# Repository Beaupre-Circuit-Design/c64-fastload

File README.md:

# Epyx FastLoad Cartridge

# Introduction

An open-source recreation of the Epyx FastLoad cartridge, this board can be used to repair a broken cartridge or build your own one. The main difference with other design are compatibility with 28 and 32 pin rom chips and bank configurability to allow multiple versions of the FastLoad rom to be installed on one cartridge.

# Compatibility

Since the design is almost identical to the original cartridge, it should have the same level of compatibility than the original FastLoad cartridge.

# Configuration

Unless dealing with special cases or custom software, J3 should be set to STD. A17 control the size of the of the EPROM, for 28 pin rom, short pin 1/2 or for 32 pin rom position 2-3 is used for bank switching.

## Bank Switching example

|A13|A14|A15|A16|A17|A18| Start of Bank |
|---|---|---|---|---|---|---------------|
|   |   |   |   |   |   |0x00000-0x01FFF|
| X |   |   |   |   |   |0x02000-0x03FFF|
|   | X |   |   |   |   |0x04000-0x05FFF|
| X | X |   |   |   |   |0x06000-0x07FFF|
|   |   | X |   |   |   |0x08000-0x09FFF|
| X |   | X |   |   |   |0x0A000-0x0BFFF|
|   | X | X |   |   |   |0x0C000-0x0DFFF|
| X | X | X |   |   |   |0x0E000-0x0FFFF|
...
|   |   |   | X |   |   |0x10000-0x11FFF|
...
|   |   |   |   | X |   |0x20000-0x21FFF|
...
|   |   |   | X | X |   |0x30000-0x31FFF|
...
|   |   |   |   |   | X |0x40000-0x41FFF|
...
|   |   |   | X |   | X |0x50000-0x51FFF|
...
|   |   |   |   | X | X |0x60000-0x61FFF|
...
|   |   |   | X | X | X |0x70000-0x71FFF|
...
| X | X | X | X | X | X |0x7E000-0x7FFFF|
| X |   | X | X | X | X |0x7A000-0x7FFFF|
|   | X | X | X | X | X |0x7C000-0x7CFFF|
| X | X | X | X | X | X |0x7E000-0x7FFFF|

# Components and assembly

[Gerbers files](Gerbers/) are available for uploading to your prefered manufacturer (I personnally use JLCPCB). In adition to the PCB, a few components must be sourced. If you want to save a few cents, R1-8 can all be 2K7 (Anything over 1K will probably work just fine too). As usual, start with the smallest components and build up (in this case, the sockets and capacitors are probably the smallest height you will have).

|Designator|Value                                |Total Quantity|
|----------|-------------------------------------|--------------|
|C1        |Ceramic Capacitor 470nF              |1             |
|C2-C3     |Ceramic Capacitor 100nF              |2             |
|R1-R7     |10K Resistor                         |7             |
|R8        |2K7 Resistor                         |1             |
|U1        |74LS07 DIP 14                        |1             |
|          |Optional DIP 14 Socket (7.62mm Wide) |1 (Optional)  |
|U2        |DIP 32 Socket (15.24mm Wide)         |1             |
|          |DIP28/32 EPROM                       |1             |
|SW1       |Push button momentary 6mm            |1             |

Once everything is assembled, program your eprom with the correct [rom image](Roms/), configure the board and you're done.

# Epyx FastLoad Manual

For reference, the Epyx FastLoad manual is available [here](Manual/).

# Licence

This work is licensed under the Creative Commons Attribution-NonCommercial-ShareAlike 4.0 International License. To view a copy of this license, visit http://creativecommons.org/licenses/by-nc-sa/4.0/ or send a letter to Creative Commons, PO Box 1866, Mountain View, CA 94042, USA.

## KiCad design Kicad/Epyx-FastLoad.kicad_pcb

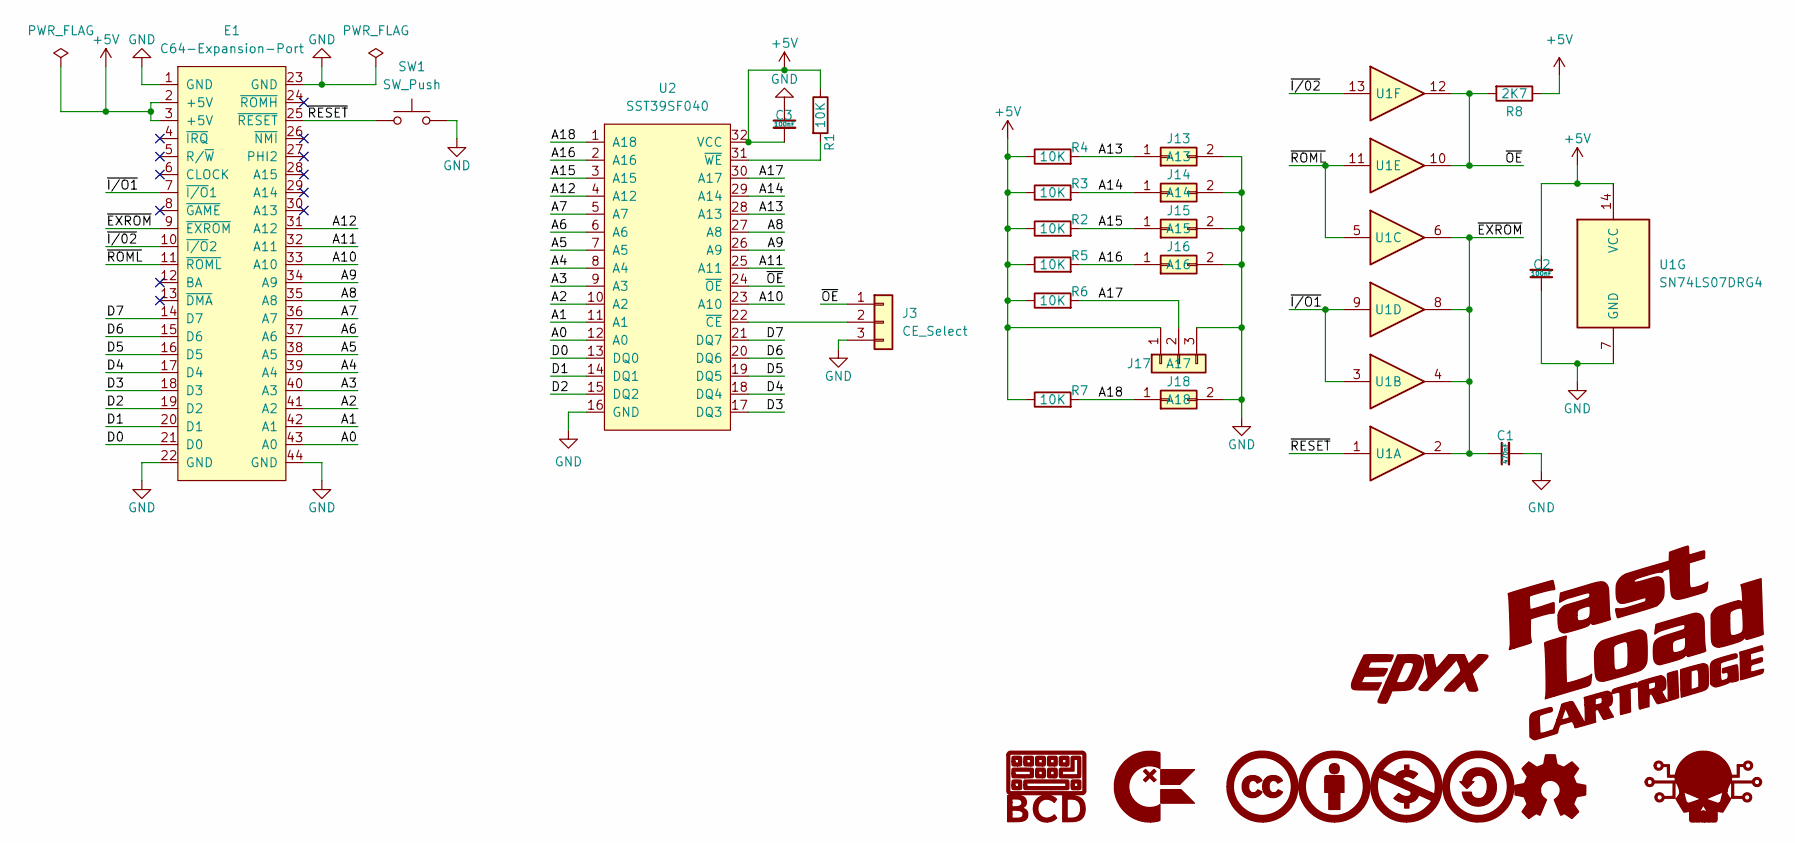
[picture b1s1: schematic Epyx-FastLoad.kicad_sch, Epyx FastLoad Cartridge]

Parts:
C1: 470nF; C_Disc_D5.0mm_W2.5mm_P5.00mm; MFR.Part # CL21B474KBFNNNE; JLCPCB Part # C13967
C2, C3: 100nF; C_Disc_D5.0mm_W2.5mm_P5.00mm; MFR.Part # CL21B104KBFNNNE; JLCPCB Part # C136621
E1: C64-Expansion-Port
G1: BCD_Logo; BCD_Logo_5mm
G2: ChickenLips; ChickenLips_5mm
G3: CreativeCommons; CreativeCommons_5mm
G4: CreativeCommons_Attribution; CreativeCommons_Attribution_5mm
G5: CreativeCommons_NonCommercial; CreativeCommons_NonCommercial_5mm
G6: CreativeCommons_ShareAlike; CreativeCommons_ShareAlike_5mm
G7: OpenSource_Hardware; Open_Source_Hardware_5mm
G8: Skull; Skull_5mm
G9: Epyx; Epyx-xsmall
G10: FastLoad; FastLoad-xsmall
J3: CE_Select; PinHeader_1x03_P2.54mm_Vertical
J13: A13; PinHeader_1x02_P2.54mm_Vertical
J14: A14; PinHeader_1x02_P2.54mm_Vertical
J15: A15; PinHeader_1x02_P2.54mm_Vertical
J16: A16; PinHeader_1x02_P2.54mm_Vertical
J17: A17; PinHeader_1x03_P2.54mm_Vertical
J18: A18; PinHeader_1x02_P2.54mm_Vertical
R1, R2, R3, R4, R5, R6, R7: 10K; R_Axial_DIN0207_L6.3mm_D2.5mm_P2.54mm_Vertical; MFR.Part # AC0805FR-0710KL; JLCPCB Part # C140868
R8: 2K7; R_Axial_DIN0207_L6.3mm_D2.5mm_P2.54mm_Vertical; MFR.Part # AC0805FR-072K7L; JLCPCB Part # C144567
SW1: SW_Push; SW_PUSH_6mm_H4.3mm
U1: SN74LS07DRG4; DIP-14_W7.62mm
U2: SST39SF040; DIP-32_W15.24mm_Socket

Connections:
+5V: C2.2, C3.2, E1.2 (+5V), E1.3 (+5V), J17.1, R1.1, R2.1, R3.1, R4.1, R5.1, R6.1, R7.1, R8.1, U1.14 (VCC), U2.32 (VCC)
/A0: E1.43 (A0), U2.12 (A0)
/A1: E1.42 (A1), U2.11 (A1)
/A2: E1.41 (A2), U2.10 (A2)
/A3: E1.40 (A3), U2.9 (A3)
/A4: E1.39 (A4), U2.8 (A4)
/A5: E1.38 (A5), U2.7 (A5)
/A6: E1.37 (A6), U2.6 (A6)
/A7: E1.36 (A7), U2.5 (A7)
/A8: E1.35 (A8), U2.27 (A8)
/A9: E1.34 (A9), U2.26 (A9)
/A10: E1.33 (A10), U2.23 (A10)
/A11: E1.32 (A11), U2.25 (A11)
/A12: E1.31 (A12), U2.4 (A12)
/A13: J13.1, R4.2, U2.28 (A13)
/A14: J14.1, R3.2, U2.29 (A14)
/A15: J15.1, R2.2, U2.3 (A15)
/A16: J16.1, R5.2, U2.2 (A16)
/A17: J17.2, R6.2, U2.30 (A17)
/A18: J18.1, R7.2, U2.1 (A18)
/D0: E1.21 (D0), U2.13 (DQ0)
/D1: E1.20 (D1), U2.14 (DQ1)
/D2: E1.19 (D2), U2.15 (DQ2)
/D3: E1.18 (D3), U2.17 (DQ3)
/D4: E1.17 (D4), U2.18 (DQ4)
/D5: E1.16 (D5), U2.19 (DQ5)
/D6: E1.15 (D6), U2.20 (DQ6)
/D7: E1.14 (D7), U2.21 (DQ7)
/~EXROM: C1.1, E1.9 (~EXROM), U1.2, U1.4, U1.6, U1.8
/~I/02: E1.10 (~I/O2), U1.13
/~I/O1: E1.7 (~I/O1), U1.3, U1.9
/~OE: J3.1, R8.2, U1.10, U1.12, U2.24 (~OE)
/~RESET: E1.25 (~RESET), SW1.1, U1.1
/~ROML: E1.11 (~ROML), U1.5, U1.11
GND: C1.2, C2.1, C3.1, E1.1 (GND), E1.22 (GND), E1.23 (GND), E1.44 (GND), J3.3, J13.2, J14.2, J15.2, J16.2, J17.3, J18.2, SW1.2, U1.7 (GND), U2.16 (GND)
unnamed: J3.2, U2.22 (~CE)
unnamed: R1.2, U2.31 (~WE)

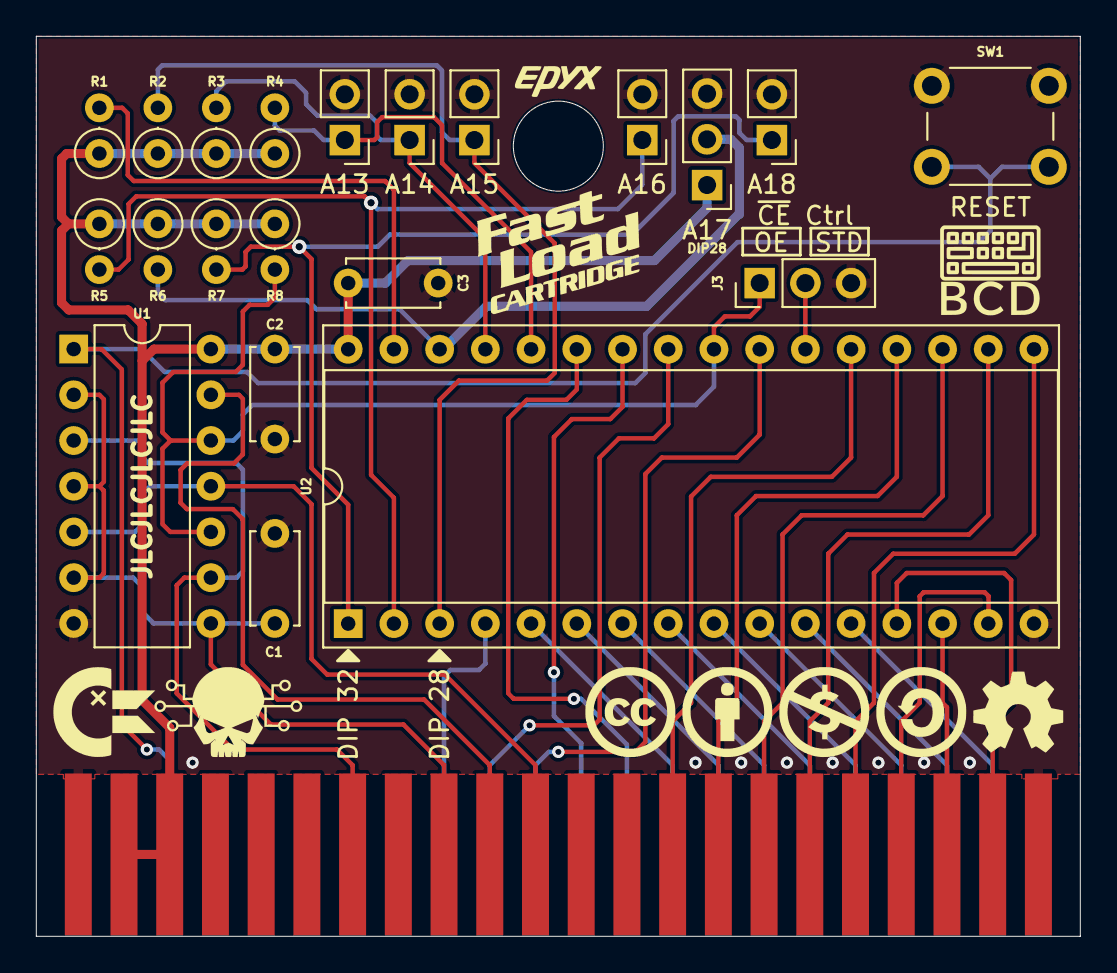
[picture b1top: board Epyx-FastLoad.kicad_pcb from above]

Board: 2 copper layers, 58.0 x 50.0 mm, 32 parts (0 on the bottom side), 37 nets.

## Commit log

2022-03-03 Add Licence.
2022-03-03 Cleanup
2022-03-03 Add smaller images
2022-03-07 Fix Typo.
